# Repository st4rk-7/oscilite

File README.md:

# Oscilite

A digital storage oscilloscope built from scratch on an STM32F407. This project covers the full stack of building a real instrument: analog signal conditioning → ADC sampling → DMA → triggering → rendering → custom PCB hardware design.

Currently running as a breadboard prototype with the V2 custom PCB shield designed and ready for fabrication.

<div align="center">
  
  <p><i>The boot splash rendered on the 160×128 ST7735 TFT at power-on.</i></p>
</div>

*The breadboard prototype running live firmware, capturing and displaying a waveform.*

## Features

- **Live waveform display** on an ILI9341 TFT with an 8×6 division graticule.
- **Hardware‑timed sampling** — a timer (TIM3) drives the ADC so every sample lands at a precise interval (timebase).
- **DMA capture** — the ADC streams samples into memory via DMA with zero CPU involvement (circular buffer on DMA2 Stream0).
- **Software triggering** — rising/falling slope with an adjustable trigger level, so the waveform locks in place instead of jittering.
- **Analog frontend** — attenuates and biases the input to safely measure bipolar signals (centered at ~1.65 V) into the MCU's 0–3.3 V ADC.
- **Automatic measurements** — min / max voltage, peak‑to‑peak, and signal frequency, shown on screen.
- **Boot splash screen** generated from an image via a custom Python pipeline.

## The Breadboard Prototype (V1)

The current working prototype proves out the entire software stack and analog theory.

*Full system context showing the STM32F407 Discovery board, the analog frontend, and the display.*

**How It Works:**
```
 Input ─▶ Analog Frontend ─▶ ADC (12‑bit) ─▶ DMA ─▶ Sample Buffer ─▶ Trigger ─▶ Display
        (attenuate + bias)   (TIM3‑timed)   (circular)              (align)    (ILI9341)
```

The input signal is attenuated and centered at ~1.65 V using an MCP6002 op-amp buffer circuit so it fits the ADC's 0–3.3 V window. A timer fires the ADC at a fixed rate to set the timebase; the DMA engine moves each sample into a circular buffer without the CPU. The firmware then finds the trigger point (rising or falling through the trigger level) and draws the aligned waveform, computing min/max/Vpp and frequency along the way.

*(A deeper write‑up of the theory is in [`docs/HowItWorks.md`](docs/HowItWorks.md))*

## Hardware Design (V2 PCB)

To move past the breadboard stage, a custom 2-layer PCB shield was designed in KiCad 10. The shield mounts directly onto the STM32F407 dev board headers, carrying the analog frontend, BNC connector, user buttons, and a header for the TFT display.

<div align="center">
  
  <p><i>The analog frontend, power distribution, and UI circuitry.</i></p>
</div>

### PCB Layout and Renders
The board is fully routed, DRC-clean, and the Gerbers are ready for manufacturing.

| Top Copper & Silkscreen | 3D Render (Top) |
|:---:|:---:|
|  |  |

| Bottom Copper | 3D Render (Bottom) |
|:---:|:---:|
|  |  |

*Note: The board relies on a dual-header layout designed specifically for the Diymore STM32F407VGT6 development board.*

## Project Structure

```
Core/Src/        Firmware: scope.c, ui.c, wave.c, adc.c, dma.c, tim.c, sandbox.c, main.c
Core/Inc/        Headers (scope.h defines grid, buffer length, trigger constants)
Drivers/         STM32 HAL + CMSIS + Display driver
pcb/fullScope/   KiCad project, layout, DRC reports, Gerbers
docs/            HowItWorks.md, PCB walkthrough
scripts/         Helper scripts (splash image conversion, UI patching)
Scopef407.ioc    STM32CubeMX configuration
```

## Building & Flashing

Prerequisites:
- [STM32CubeMX](https://www.st.com/en/development-tools/stm32cubemx.html) (config is in `Scopef407.ioc`)
- ARM GNU toolchain (`arm-none-eabi-gcc`)
- CMake ≥ 3.22 and Ninja
- A flashing tool: STM32CubeProgrammer, OpenOCD, or st-link

Build:
```bash
# Configure (uses the provided CMake presets)
cmake --preset Debug

# Build
cmake --build build/Debug
```

Flash it with your tool of choice, e.g.:
```bash
st-flash write build/Debug/Scopef407.bin 0x8000000
```

## Project Status & Phases

- **Phase 1 (Complete):** Breadboard prototype, firmware architecture (ADC/DMA/Trigger), and UI rendering.
- **Phase 2 (Current):** Custom PCB shield designed, DRC-verified, and Gerbers generated.
- **Phase 3 (Next):** PCB fabrication, assembly, and testing of the final standalone hardware unit.

This is intentionally a hands-on learning project to understand the full stack of instrument creation, not a precision lab tool.

## Acknowledgments
Built on the STM32 HAL and CMSIS.

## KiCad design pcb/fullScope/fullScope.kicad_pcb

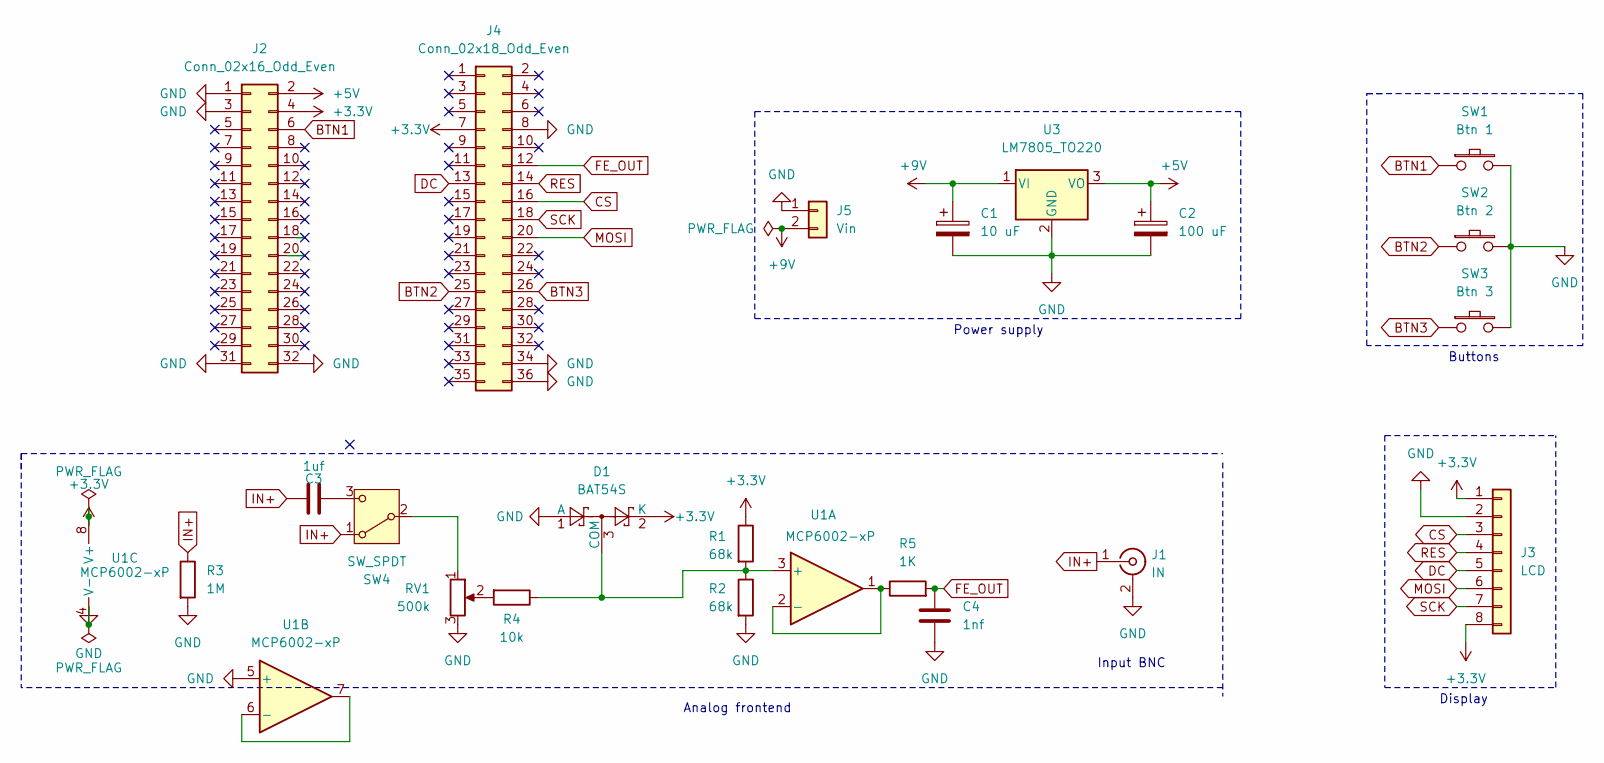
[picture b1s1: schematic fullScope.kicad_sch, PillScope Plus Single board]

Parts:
C1: 10 uF; CP_Radial_D5.0mm_P2.00mm
C2: 100 uF; CP_Radial_D5.0mm_P2.00mm
C3: 1uf; C_Disc_D5.0mm_W2.5mm_P5.00mm
C4: 1nf; C_Disc_D5.0mm_W2.5mm_P5.00mm
D1: BAT54S; SOT-23
J1: IN; BNC_Amphenol_B6252HB-NPP3G-50_Horizontal
J2: Conn_02x16_Odd_Even; PinSocket_2x16_P2.54mm_Vertical
J3: LCD; PinHeader_1x08_P2.54mm_Vertical
J4: Conn_02x18_Odd_Even; PinSocket_2x18_P2.54mm_Vertical
J5: Vin; PinHeader_1x02_P2.54mm_Vertical
R1, R2: 68k; R_Axial_DIN0207_L6.3mm_D2.5mm_P7.62mm_Horizontal
R3: 1M; R_Axial_DIN0207_L6.3mm_D2.5mm_P7.62mm_Horizontal
R4: 10k; R_Axial_DIN0207_L6.3mm_D2.5mm_P7.62mm_Horizontal
R5: 1K; R_Axial_DIN0207_L6.3mm_D2.5mm_P7.62mm_Horizontal
RV1: 500k; Potentiometer_Bourns_3296W_Vertical
SW1: Btn 1; SW_PUSH-12mm
SW2: Btn 2; SW_PUSH-12mm
SW3: Btn 3; SW_PUSH-12mm
SW4: SW_SPDT; SW_Slide_SPDT_Straight_CK_OS102011MS2Q
U1: MCP6002-xP; DIP-8_W7.62mm
U3: LM7805_TO220; TO-220-3_Horizontal_TabDown

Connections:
+3.3V: D1.2 (K), J2.4, J3.1, J3.8, J4.7, R1.1, U1.8 (V+)
+5V: C2.1, J2.2, U3.3 (VO)
+9V: C1.1, J5.2, U3.1 (VI)
BTN1: J2.6, SW1.1
BTN2: J4.25, SW2.1
BTN3: J4.26, SW3.1
CS: J3.3, J4.16
DC: J3.5, J4.13
FE_OUT: C4.1, J4.12, R5.2
GND: C1.2, C2.2, C4.2, D1.1 (A), J1.2 (Ext), J2.1, J2.3, J2.31, J2.32, J3.2, J4.8, J4.34, J4.36, J5.1, R2.2, R3.2, RV1.3, SW1.2, SW2.2, SW3.2, U1.4 (V-), U1.5 (+), U3.2 (GND)
IN+: C3.2, J1.1 (In), R3.1, SW4.1 (A)
MOSI: J3.6, J4.20
unnamed: D1.3 (COM), R1.2, R2.1, R4.1, U1.3 (+)
unnamed: R4.2, RV1.2
unnamed: RV1.1, SW4.2 (B)
unnamed: C3.1, SW4.3 (C)
unnamed: R5.1, U1.1, U1.2 (-)
unnamed: U1.6 (-), U1.7
RES: J3.4, J4.14
SCK: J3.7, J4.18

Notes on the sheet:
Buttons
Power supply
Input BNC
Display
Analog frontend

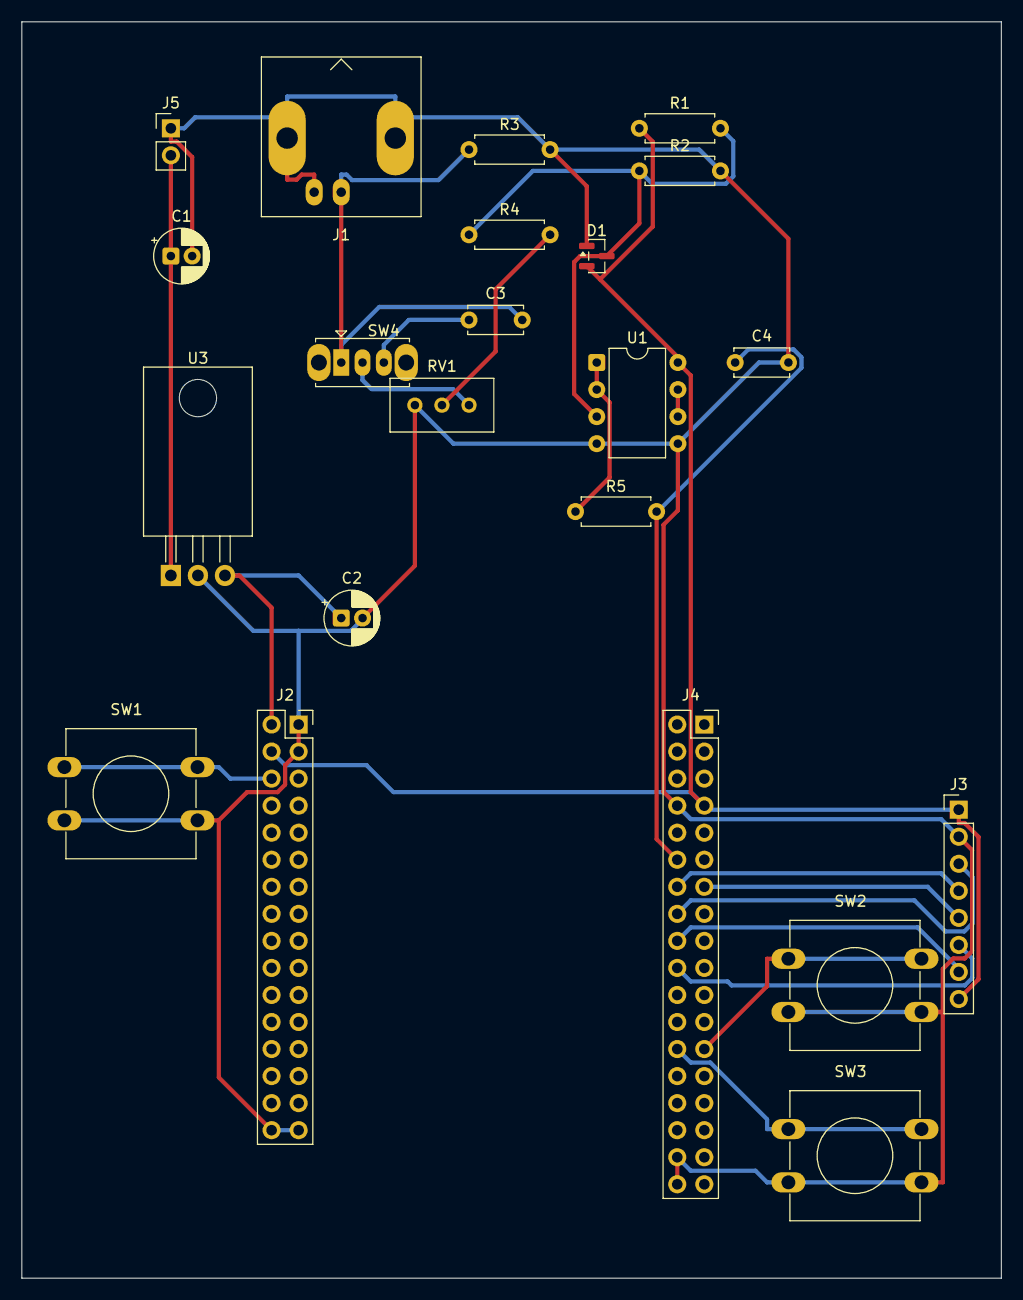
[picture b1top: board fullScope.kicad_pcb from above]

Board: 2 copper layers, 92.0 x 118.0 mm, 22 parts (0 on the bottom side), 20 nets.

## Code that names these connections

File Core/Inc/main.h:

/* USER CODE BEGIN Header */
/**
  ******************************************************************************
  * @file           : main.h
  * @brief          : Header for main.c file.
  *                   This file contains the common defines of the application.
  ******************************************************************************
  * @attention
  *
  * Copyright (c) 2026 STMicroelectronics.
  * All rights reserved.
  *
  * This software is licensed under terms that can be found in the LICENSE file
  * in the root directory of this software component.
  * If no LICENSE file comes with this software, it is provided AS-IS.
  *
  ******************************************************************************
  */
/* USER CODE END Header */

/* Define to prevent recursive inclusion -------------------------------------*/
#ifndef __MAIN_H
#define __MAIN_H

#ifdef __cplusplus
extern "C" {
#endif

/* Includes ------------------------------------------------------------------*/
#include "stm32f4xx_hal.h"

/* Private includes ----------------------------------------------------------*/
/* USER CODE BEGIN Includes */

/* USER CODE END Includes */

/* Exported types ------------------------------------------------------------*/
/* USER CODE BEGIN ET */

/* USER CODE END ET */

/* Exported constants --------------------------------------------------------*/
/* USER CODE BEGIN EC */

/* USER CODE END EC */

/* Exported macro ------------------------------------------------------------*/
/* USER CODE BEGIN EM */

/* USER CODE END EM */

/* Exported functions prototypes ---------------------------------------------*/
void Error_Handler(void);

/* USER CODE BEGIN EFP */

/* USER CODE END EFP */

/* Private defines -----------------------------------------------------------*/
#define Button_Pin GPIO_PIN_15
#define Button_GPIO_Port GPIOD
#define LED_Pin GPIO_PIN_0
#define LED_GPIO_Port GPIOE

/* USER CODE BEGIN Private defines */

// Buttons (temporary - will be assigned to real pins when hardware arrives)
#define BTN1_Pin GPIO_PIN_7
#define BTN1_GPIO_Port GPIOB
#define BTN2_Pin GPIO_PIN_8
#define BTN2_GPIO_Port GPIOB
#define BTN3_Pin GPIO_PIN_9
#define BTN3_GPIO_Port GPIOB

// ST7735 Display pins (directly connected, no SPI chip-select needed)
#define ST7735_CS_Pin GPIO_PIN_4
#define ST7735_CS_GPIO_Port GPIOA
#define ST7735_DC_Pin GPIO_PIN_3
#define ST7735_DC_GPIO_Port GPIOA
#define ST7735_RES_Pin GPIO_PIN_2
#define ST7735_RES_GPIO_Port GPIOA

/* USER CODE END Private defines */

#ifdef __cplusplus
}
#endif

#endif /* __MAIN_H */

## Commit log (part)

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2026-06-05 init
2026-06-08 feat:sandbox & splash
2026-06-08 fix: ui bugs
2026-06-10 feat(ui): patch scripts and assets
